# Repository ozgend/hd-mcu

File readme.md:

# hd-mcu

## bluetooth supported mcu for harley davidson 99-03 with raspberry pi pico

this is not a ecu but a diy -and for fun- project for a monitoring hardware via an mcu since there is no [can-bus](https://en.wikipedia.org/wiki/CAN_bus) support for 99-03 models. it replaces the default turn signal module (tsm) to provide monitoring features for battery voltage, rpm, voes, ignition, and external thermo sensors via bluetooth to the mobile application. it does not involve a reverse engineering for the original hd-tsm module.

- programmable idle timeout for turn signal
- pcb provides signal switching via h-bridge module or mosfet + oc
- built-in battery voltage sensor
- built-in rpm reader
- built-in temperature sensor via rpi-pico
- aux inputs for ignition and voes signals _(may require custom ignition module ie. [ultima/dyna 2000i](./doc/ud2000i.pdf))_
- vehicle information with editable fields for maintenance records
- external 6x thermocpouler raiser for max6670
- supports up to 8x thermocpouler sensors for various purposes

### features

- [x] hardware serial
  - [x] raw ft232 usb serial
- [x] bluetooth serial
  - [x] raw bluetooth serial (hc-06 @ 9600 bps)
  - [x] mobile app
- [x] data polling/broadcasting
  - [x] reduced power consumption
  - [x] reduced cpu clock usage
- [x] turn signal flasher module
  - [x] left/right turn signal flasher
  - [x] hazard flasher
  - [x] flash on startup
  - [x] adjustable flash rate
- [x] throttle control module
  - [x] linear hall sensor input
  - [x] servo pwm output
  - [x] adjustable base parameters
  - [x] adjustable idle speed
  - [ ]
  - [ ] adjustable throttle curves
- [x] supported sensor inputs
  - [x] multiplexed thermocouples
    - [x] up to 8 thermocouples
  - [x] direct sensor inputs
    - [x] uptime counter (onboard)
    - [x] mcu voltage (onboard)
    - [x] temperature (onboard)
    - [x] vbus input (onboard)
    - [x] battery voltage input
    - [x] rpm input
    - [x] speed input
  - [ ] tpms
    - [ ] 433mhz receiver implementation
    - [ ] tpms decoder / man-i or man-ii (tbd)
  - [ ] ignition module
    - [ ] dyna 2000i / ultima 2000i timer & pickup
    - [ ] programmable ignition advance
      - [ ] advance curve
      - [ ] temp compensation
      - [ ] rpm compensation
      - [ ] wideband o2 sensor for afr

### software

**mobile app**

- platform

  - `react 18.2.0`
  - `react-native: 0.73.2`

- react-native
  - [x] android
  - [ ] ios

### mobile app ui

**mcu firmware**

- platform

  - `nodejs: 20`
  - [`kaluma-cli: 1.4.0`](https://kalumajs.org/docs/getting-started)
  - [`kalumajs runtime: 1.2.1`](https://kalumajs.org/download/)

- FLASH: 2044/24 kb
- SRAM: 264 total, 184/62 kb

### hardware

**assembly**

- 12v-5v buck converter / switching regulator
  - [lm2596 datasheet](./doc/lm2596.pdf)
- raspberry pi pico
  - [pinout](https://pico.pinout.xyz/)
  - [datasheet](./doc/pico-datasheet.pdf)
- hc-06 bluetooth module
  - [datasheet](./doc/hc06.pdf)
- `TSM` / turn signal module
  - _(option-1)_ - with mosfet extension board
    - _pick this if your rectifier is 3 pin and charge flux is 12v-15v_
    - [IRF4905 datasheet](./doc/IRF4905.pdf)
  - _(option-2)_ - l298n h-bridge driver module
    - [datasheet](./doc/l298.pdf)
- `THE` / thermocouple module
  - cd4051 multiplexer
    - [datasheet](./doc/cd4051b.pdf)
  - max6675 thermocouple digitizer
    - [datasheet](./doc/MAX6675.pdf)
    - k-type thermocouple (maximum of 8)
- `TCM` / throttle control module
  - [linear hall sensor / 49e](./doc/49e.pdf)
  - [DS3230MG digital servo](./doc/ds3230.pdf)
- 5v super capacitor
- 5805 voltage regulator
- 33k resistor
- 10k resistor
- 7.5k resistor
- 4.7k resistor
- 1k resistor
- 1n4001 diode

### pcb

**front**

**back**

**blueprint**

### setup & building & installing

- initialization

  ```bash
  git clone
  npm run install
  ```

- cook everything

  ```bash
  npm run build
  ```

- create mcu firmware

  ```bash
  npm build:mcu
  ```

- flash firmware to pico

  ```bash
  npm run flash:mcu -- /dev/tty.usbmodem2XXX
  ```

- create mobile app

  - _create local build_

    ```bash
    npm run build:app
    ```

  - _create distributable bundle .apk_

    ```bash
    nom run bundle:app
    ```

## usb serial interface

- usb: `115200 bps`
- bt: `9600 bps`

### service interaction

- query only: `[SVC]+[CMD]\n`
- set svc data: `[SVC]+[CMD]=[DATA]\n`

**service list:**
| service | description |
| ------- | ----------- |
| `SYS` | mcu information system |
| `THE` | thermocouple sensor module |
| `TSM` | turn signal module |
| `TCM` | throttle control module |
| `VHC` | vehicle healthcheck module |
| `VHI` | vehicle information system |

**command list**
| command | description |
| ------- | ----------- |
| `INFO` | get information from service|
| `DATA` | get data from service |
| `SET` | send data to service |
| `START` | start monitoring |
| `STOP` | stop monitoring |

**`TSM` extended command set**
| command | description |
| ------- | ----------- |
| `LEFT` | left turn signal |
| `RIGHT` | right turn signal |
| `ALL` | hazard signal |
| `NONE` | turn signal off |

### module interaction

- query only: `[MOD]+[CMD]\n`

**module list:**
| name | description |
| ------- | ----------- |
| `M0` | main mcu module |

**command list**
| command | description |
| ------- | ----------- |
| `DIAG` | execute diagnostic |
| `START` | start ON_DEMAND services in module and publish data |
| `STOP` | stop ON_DEMAND services in module and stop publishing data |
| `LIST_ALL` | list all registered services in module |
| `LIST_RUN` | list running/active services in module |

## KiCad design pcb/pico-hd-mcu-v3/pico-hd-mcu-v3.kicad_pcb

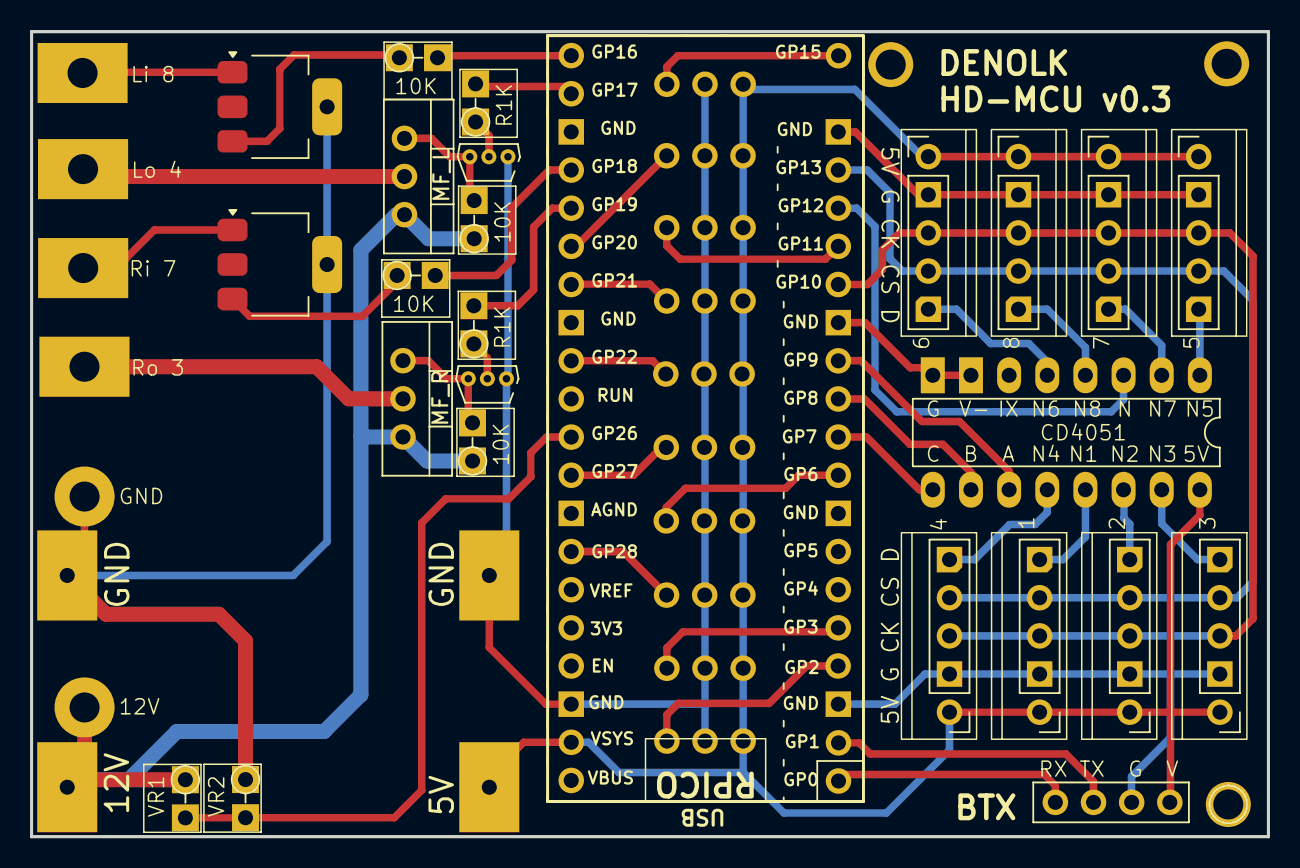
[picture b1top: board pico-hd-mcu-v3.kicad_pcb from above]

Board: 2 copper layers, 82.4 x 53.6 mm, 17 parts (0 on the bottom side), 18 nets.

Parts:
1: N1; Socker_PinHeader_1x05_P2.54mm_Dualside
2, 3, 4, 5: N4; Socker_PinHeader_1x05_P2.54mm_Dualside
6: N6; Socker_PinHeader_1x05_P2.54mm_Dualside
7: N7; Socker_PinHeader_1x05_P2.54mm_Dualside
8: N8; Socker_PinHeader_1x05_P2.54mm_Dualside
10K, 10K#2, 10K#3, 10K#4: R_Axial_DIN0204_L3.6mm_D1.6mm_P2.54mm_Vertical
CD4051: CD4051; DIP-16_W7.62mm_LongPads
R1K, R1K#2: R_Axial_DIN0204_L3.6mm_D1.6mm_P2.54mm_Vertical
VR1, VR2: R_Axial_DIN0204_L3.6mm_D1.6mm_P2.54mm_Vertical

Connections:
5V: 1.1, 2.1, 3.1, 4.1, 5.1, 6.1, 7.1, 8.1, CD4051.16
12V: 10K#2.1, 10K#4.1, VR1.1
D_CS: 1.4, 2.4, 3.4, 4.4, 5.4, 6.4, 7.4, 8.4
D_SCK: 1.3, 2.3, 3.3, 4.3, 5.3, 6.3, 7.3, 8.3
D_SIG_L_IN: 10K.1, 10K.2
D_SIG_L_OUT: R1K#2.1, R1K#2.2
D_SIG_R_IN: 10K#3.1, 10K#3.2
D_SIG_R_OUT: R1K.1, R1K.2
D_VOLT: VR1.2, VR2.2
GND: 1.2, 2.2, 3.2, 4.2, 5.2, 6.2, 7.2, 8.2, CD4051.7, CD4051.8, VR2.1
MUX_S1: 1.5, CD4051.13
MUX_S2: 2.5, CD4051.14
MUX_S3: 3.5, CD4051.15
MUX_S4: 4.5, CD4051.12
MUX_S5: 5.5, CD4051.1
MUX_S6: 6.5, CD4051.5
MUX_S7: 7.5, CD4051.2
MUX_S8: 8.5, CD4051.4

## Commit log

2023-12-13 optimize memory usage 1700b to 570b
2023-12-14 optimize pin assignments
2023-12-14 remove pin map
2023-12-14 refactoring (#1)
    * optimize memory usage 1700b to 570b
    * optimize pin assignments
    * remove pin map
2023-12-15 hw pin update
2023-12-15 update pinout
2023-12-15 add pcb blueprint
2023-12-15 refactor Ax sensor pin layout
2023-12-15 pcb routing optimize
2023-12-15 image update
2023-12-15 pcb unified (#2)
    * hw pin update
    * update pinout
    * add pcb blueprint
    * update readme
    * refactor Ax sensor pin layout
    * pcb routing optimize
2023-12-15 renaming & refactoring
2023-12-15 add base service log
2023-12-15 add system stats
2023-12-15 optimizations log (#3)
    * add base service log
    * add system stats
2023-12-15 uptime counter to dct
2023-12-15 service runtime refactoring
2023-12-15 service runtime command dispatch
2023-12-15 add serial commands
2023-12-15 fix peripheral alloc
2023-12-15 serialize json & stream at once per service
2023-12-15 switch to index based keys
2023-12-15 remote tsm
2023-12-15 serial commands (#4)
    * add serial commands
    * fix peripheral alloc
    * serialize json & stream at once per service
    * switch to index based keys
    * remote tsm
2023-12-16 update pcb
2023-12-18 update bt serial
2023-12-19 fix serial com sw
2023-12-19 Serial commands (#5)
    * add serial commands
    * fix peripheral alloc
    * serialize json & stream at once per service
    * switch to index based keys
    * remote tsm
    * update pcb
2023-12-19 wip pcb
2023-12-21 restructure files
2023-12-21 wip - pico port nodejs
2023-12-22 exclude bundle.js
2023-12-22 ref pin
2023-12-22 pinmap fix
2023-12-22 fix uart data rx
2023-12-22 add service type auto run
2023-12-22 add tsm irq
2023-12-25 add common logger and events
2023-12-25 custom lib hc4051 mux
2023-12-25 custom lib max6675 thermo
2023-12-25 add muxed sensor service
2023-12-25 refactor gpio assignments
2023-12-25 refactoring lifecycle
2023-12-25 lib error logs
2023-12-25 mux update rate
2023-12-25 reset timer clock rtc
2023-12-25 spi hw/sw
2023-12-25 max6675 wip fix
2023-12-25 pico purple board pinout
2023-12-25 muxed thermo fix
2023-12-25 fix data payload
2023-12-25 tsm blink debugger
2023-12-25 tsm interrupt wip
2023-12-25 working state tsm
2023-12-26 bus logiinfo
2023-12-26 add ref docs
2023-12-26 update readme + src folders
2023-12-26 master merge fix
2024-01-04 update serial data schema
2024-01-04 calculate dev adc sensors
2024-01-09 update mcu according to pico gpio
2024-01-09 update voltage divider
2024-01-17 update ignore
2024-01-17 initialize react native mobile app
2024-01-17 refactor rx mobile app
2024-01-17 fix bt handshake
2024-01-17 ui improvements
2024-01-17 fix value formatting
2024-01-17 fix visual
2024-01-17 remove ttf
2024-01-17 fix + improve bt serial comm data
2024-01-18 shared rx tsx refactoring
2024-01-18 serial payload opt
2024-01-18 make mcu services available to poll data
2024-01-18 refactor to work with polled device data and info
2024-01-18 add bt device discovery
2024-01-18 improve bt connection ux
2024-01-19 add device discovery for bonded devices only
2024-01-19 reformat js
2024-01-22 refactor commands
2024-01-22 order field info
2024-01-23 fix bt serial comm & discovery
2024-01-23 refactor common schema, rename services
2024-01-23 add vehicle info service
2024-01-23 editable vehicle info
2024-01-23 update views
2024-01-23 refactor views
2024-01-23 more sensor values & info edit
2024-02-07 pcb update
2024-04-30 remove dup readme
2024-04-30 drop arduino nano support
2024-04-30 update bundling scripts
2024-04-30 update mock data provider
2024-05-01 add pcb plots
2024-05-01 refactor imports
2024-05-01 update feature readme
2024-05-01 add persist vi for mock data provider
2024-05-01 fix vehicle info view
2024-05-01 updatee vehicle info props
2024-05-01 fix data types for fields
2024-05-01 add service info toggling + ui improvements
2024-05-01 shared constants
2024-05-02 fix rxn metro ref path
2024-05-02 update package commands
2024-05-02 code cleanup
2024-05-02 refactor data value formatting
2024-05-02 add autostart service
2024-05-06 udpate ui labels
2024-05-07 added 12v5 power supply submodule
2024-05-07 update plots
2024-05-07 updat pcb add drill holes
2024-05-09 add extension board for mux x4
2024-05-09 pcb fix drc exclusion
2024-05-09 remove ms codepush
2024-05-09 fix missing constants
2024-05-09 build optimizations + refactoring
2024-05-20 update pcb - ext mosfet switch
2024-05-21 app settings storage with themes
2024-05-21 update appConfig and ui
2024-05-21 fix ui update theme change
2024-05-21 add config for home, fix ui
2024-05-21 update icons
2024-05-21 fix tsm service
2024-05-21 fix vhi filename
2024-05-21 fix vhc adc temp sensor
2024-05-21 add rxn bundle cmd
2024-05-21 update rxn android bundle
2024-05-22 fix progress ui
2024-05-22 add schema version, add pollms fields, fix uptime, fix edit numerics
2024-05-22 fix active tab theming
2024-05-22 add bash scripts
2024-05-24 update bundle
2024-05-24 improve turn signal service
2024-05-24 remove debug log
2024-05-25 add heartbeat pulse
2024-05-27 fix heartbeat
2024-05-28 update plot
2024-05-28 introduce mcu settings
2024-05-29 add onboard vref reading
2024-05-29 fix ts/js gen
2024-05-29 add mcu vref
2024-05-29 onboard led
2024-05-29 fix spi handler
2024-05-29 fix runsh
2024-05-29 update schema
2024-06-17 fix config lowecase
2024-08-29 update readme and refs
2024-08-29 add ignition doc
2024-08-29 add gplv3
2024-08-29 add instructions to run/build/flash
2024-08-29 add tpms todo
2024-08-29 add rf433 refs
2024-10-30 fix adc vref and adc0 reading + scaling
2024-10-30 set vhc unimplemented to -1
2024-10-30 fix setup vs start
2024-10-30 remove ar nano
2024-11-01 add rpm counter
2024-11-08 set bt at+name
2024-11-08 fix module service commands
2024-11-08 toggle onboard led for diag
2024-11-08 add command + service readme
2024-11-08 update diag tsm
2024-11-11 adjust tsm interrupts & timing
2024-11-11 extend rw tsm interrupt and timing config
2024-11-11 add tsm interrupt button as input_pullup
2024-11-13 port ts
2024-11-18 relocate js project files
2024-11-19 clean ts dist
2024-11-19 cleanup bundle
2024-11-19 fix fs ops
2024-11-19 fix refactor
2025-05-21 ignore bundle folder
2025-05-21 tsm hazard fix
2025-05-27 rm dist
2025-05-27 fix tsm hazard flash
2025-05-29 remove prebuilt ts-schema/*.js
2025-05-29 add ignition module stub
2025-05-29 fix webpack kaluma fs bundling
2025-05-29 add diag and debug
2025-05-29 ignition module readme stub
2025-05-29 pin assignment for ign module
2025-06-04 add startup diagnostics
2025-06-04 fix file handling
2025-06-04 check empty/invalid event.serial data
2025-06-04 check debounce for hazard lights
2025-06-04 change ts compile to es2017
2025-06-04 add usb detection over vbus/gpio24
2025-07-25 remove js app
2025-10-01 fix adc reading
2025-10-01 init pcbv3
2025-12-29 update build and simple test module
2025-12-29 fix runtime services and temperature reading
2025-12-29 add throttle controller
2025-12-29 update throttle servo controller
2025-12-30 pcbv3 stub
2026-01-05 refactor - adc hall sensor
2026-01-06 mcu - improve throttle controller
2026-01-06 mcu - refactoring event handler and logger
2026-01-06 mcu - gpio remapping
2026-01-06 app - throttle control data view
2026-01-06 udpate docs
2026-01-06 pcb - v3 wip
2026-01-06 hardware gpio remapping
2026-01-06 mcu - remove eslint-disable
2026-01-06 update pcb v3
2026-01-06 fallback to uart0 for bt rx/tx
